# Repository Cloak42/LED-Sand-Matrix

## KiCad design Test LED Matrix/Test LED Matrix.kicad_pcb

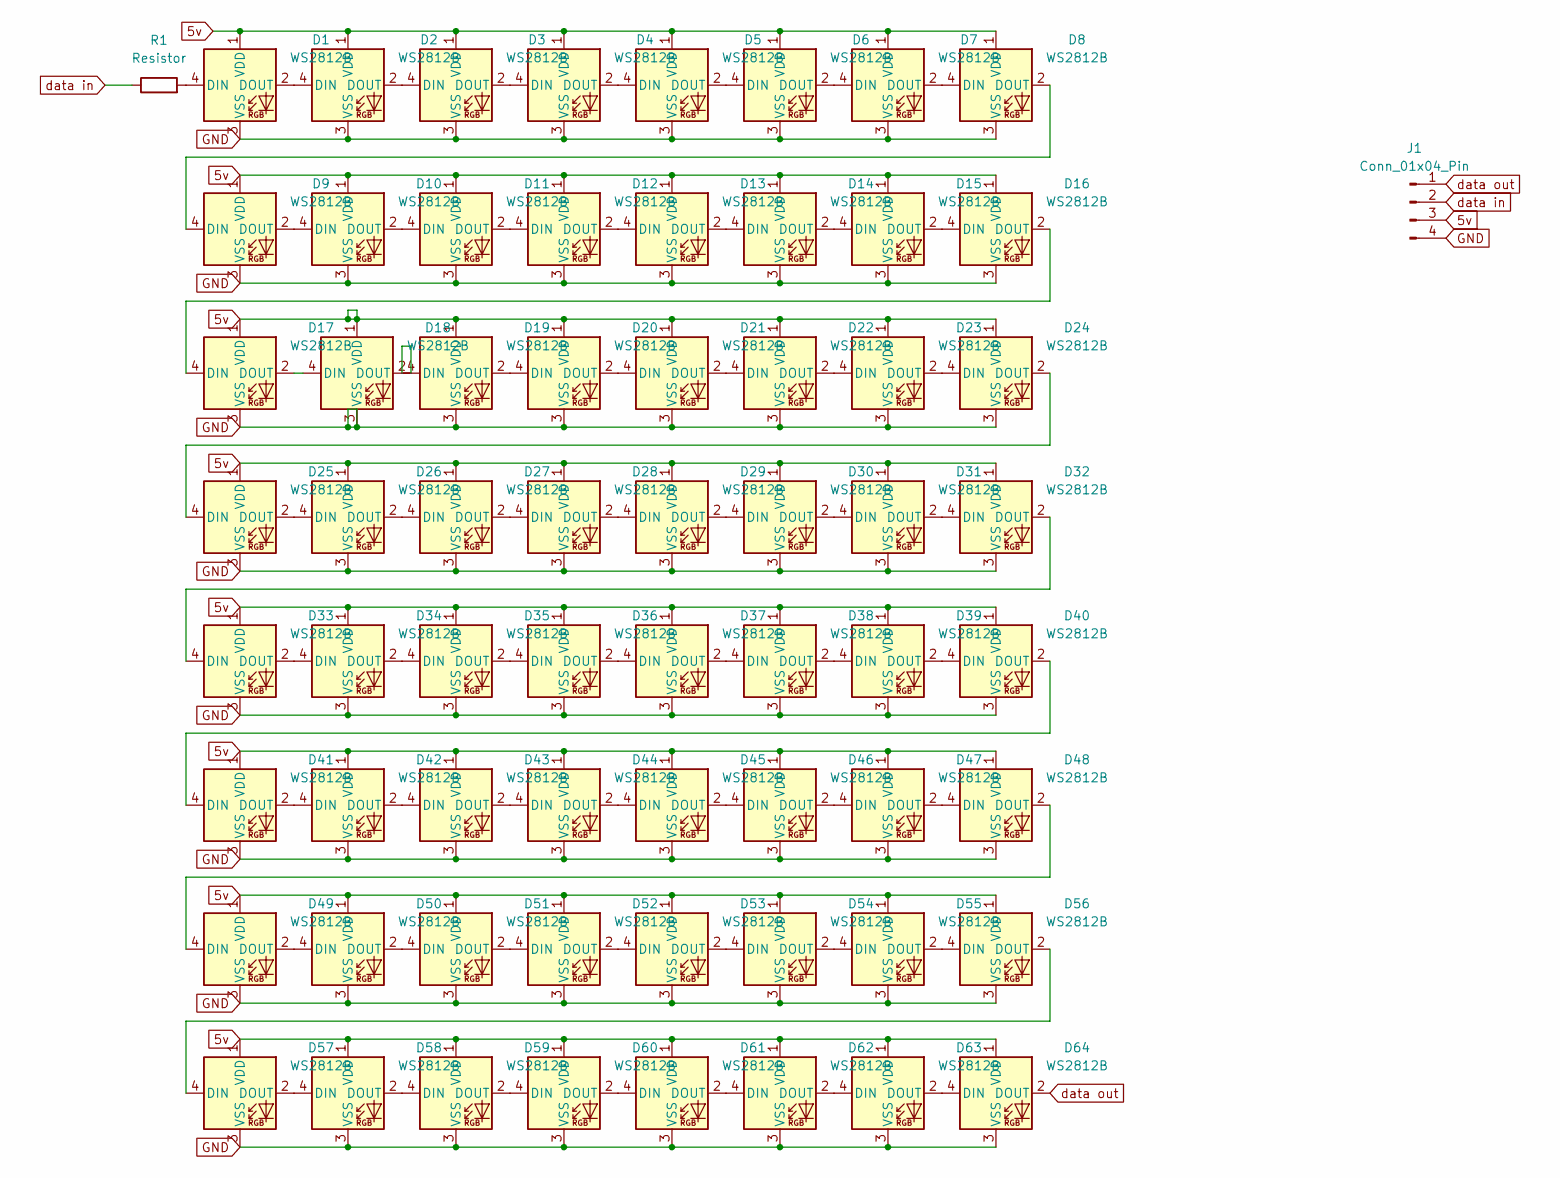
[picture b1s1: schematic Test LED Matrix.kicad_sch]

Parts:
D1, D2, D3, D4, D5, D6, D7, D8, D9, D10, D11, D12, D13, D14, D15, D16, D17, D18, D19, D20, D21, D22, D23, D24, D25, D26, D27, D28, D29, D30, D31, D32, D33, D34, D35, D36, D37, D38, D39, D40, D41, D42, D43, D44, D45, D46, D47, D48, D49, D50, D51, D52, D53, D54, D55, D56, D57, D58, D59, D60, D61, D62, D63, D64: WS2812B; LED_WS2812B_PLCC4_5.0x5.0mm_P3.2mm
J1: Conn_01x04_Pin; PinSocket_1x04_P2.54mm_Vertical
R1: Resistor; R_Axial_DIN0204_L3.6mm_D1.6mm_P5.08mm_Horizontal

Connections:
5v: D1.1 (VDD), D2.1 (VDD), D3.1 (VDD), D4.1 (VDD), D5.1 (VDD), D6.1 (VDD), D7.1 (VDD), D8.1 (VDD), D9.1 (VDD), D10.1 (VDD), D11.1 (VDD), D12.1 (VDD), D13.1 (VDD), D14.1 (VDD), D15.1 (VDD), D16.1 (VDD), D17.1 (VDD), D18.1 (VDD), D19.1 (VDD), D20.1 (VDD), D21.1 (VDD), D22.1 (VDD), D23.1 (VDD), D24.1 (VDD), D25.1 (VDD), D26.1 (VDD), D27.1 (VDD), D28.1 (VDD), D29.1 (VDD), D30.1 (VDD), D31.1 (VDD), D32.1 (VDD), D33.1 (VDD), D34.1 (VDD), D35.1 (VDD), D36.1 (VDD), D37.1 (VDD), D38.1 (VDD), D39.1 (VDD), D40.1 (VDD), D41.1 (VDD), D42.1 (VDD), D43.1 (VDD), D44.1 (VDD), D45.1 (VDD), D46.1 (VDD), D47.1 (VDD), D48.1 (VDD), D49.1 (VDD), D50.1 (VDD), D51.1 (VDD), D52.1 (VDD), D53.1 (VDD), D54.1 (VDD), D55.1 (VDD), D56.1 (VDD), D57.1 (VDD), D58.1 (VDD), D59.1 (VDD), D60.1 (VDD), D61.1 (VDD), D62.1 (VDD), D63.1 (VDD), D64.1 (VDD), J1.3
GND: D1.3 (VSS), D2.3 (VSS), D3.3 (VSS), D4.3 (VSS), D5.3 (VSS), D6.3 (VSS), D7.3 (VSS), D8.3 (VSS), D9.3 (VSS), D10.3 (VSS), D11.3 (VSS), D12.3 (VSS), D13.3 (VSS), D14.3 (VSS), D15.3 (VSS), D16.3 (VSS), D17.3 (VSS), D18.3 (VSS), D19.3 (VSS), D20.3 (VSS), D21.3 (VSS), D22.3 (VSS), D23.3 (VSS), D24.3 (VSS), D25.3 (VSS), D26.3 (VSS), D27.3 (VSS), D28.3 (VSS), D29.3 (VSS), D30.3 (VSS), D31.3 (VSS), D32.3 (VSS), D33.3 (VSS), D34.3 (VSS), D35.3 (VSS), D36.3 (VSS), D37.3 (VSS), D38.3 (VSS), D39.3 (VSS), D40.3 (VSS), D41.3 (VSS), D42.3 (VSS), D43.3 (VSS), D44.3 (VSS), D45.3 (VSS), D46.3 (VSS), D47.3 (VSS), D48.3 (VSS), D49.3 (VSS), D50.3 (VSS), D51.3 (VSS), D52.3 (VSS), D53.3 (VSS), D54.3 (VSS), D55.3 (VSS), D56.3 (VSS), D57.3 (VSS), D58.3 (VSS), D59.3 (VSS), D60.3 (VSS), D61.3 (VSS), D62.3 (VSS), D63.3 (VSS), D64.3 (VSS), J1.4
unnamed: D1.4 (DIN), R1.2
unnamed: D1.2 (DOUT), D2.4 (DIN)
unnamed: D2.2 (DOUT), D3.4 (DIN)
unnamed: D3.2 (DOUT), D4.4 (DIN)
unnamed: D4.2 (DOUT), D5.4 (DIN)
unnamed: D5.2 (DOUT), D6.4 (DIN)
unnamed: D6.2 (DOUT), D7.4 (DIN)
unnamed: D7.2 (DOUT), D8.4 (DIN)
unnamed: D8.2 (DOUT), D9.4 (DIN)
unnamed: D9.2 (DOUT), D10.4 (DIN)
unnamed: D10.2 (DOUT), D11.4 (DIN)
unnamed: D11.2 (DOUT), D12.4 (DIN)
unnamed: D12.2 (DOUT), D13.4 (DIN)
unnamed: D13.2 (DOUT), D14.4 (DIN)
unnamed: D14.2 (DOUT), D15.4 (DIN)
unnamed: D15.2 (DOUT), D16.4 (DIN)
unnamed: D16.2 (DOUT), D17.4 (DIN)
unnamed: D17.2 (DOUT), D18.4 (DIN)
unnamed: D18.2 (DOUT), D19.4 (DIN)
unnamed: D19.2 (DOUT), D20.4 (DIN)
unnamed: D20.2 (DOUT), D21.4 (DIN)
unnamed: D21.2 (DOUT), D22.4 (DIN)
unnamed: D22.2 (DOUT), D23.4 (DIN)
unnamed: D23.2 (DOUT), D24.4 (DIN)
unnamed: D24.2 (DOUT), D25.4 (DIN)
unnamed: D25.2 (DOUT), D26.4 (DIN)
unnamed: D26.2 (DOUT), D27.4 (DIN)
unnamed: D27.2 (DOUT), D28.4 (DIN)
unnamed: D28.2 (DOUT), D29.4 (DIN)
unnamed: D29.2 (DOUT), D30.4 (DIN)
unnamed: D30.2 (DOUT), D31.4 (DIN)
unnamed: D31.2 (DOUT), D32.4 (DIN)
unnamed: D32.2 (DOUT), D33.4 (DIN)
unnamed: D33.2 (DOUT), D34.4 (DIN)
unnamed: D34.2 (DOUT), D35.4 (DIN)
unnamed: D35.2 (DOUT), D36.4 (DIN)
unnamed: D36.2 (DOUT), D37.4 (DIN)
unnamed: D37.2 (DOUT), D38.4 (DIN)
unnamed: D38.2 (DOUT), D39.4 (DIN)
unnamed: D39.2 (DOUT), D40.4 (DIN)
unnamed: D40.2 (DOUT), D41.4 (DIN)
unnamed: D41.2 (DOUT), D42.4 (DIN)
unnamed: D42.2 (DOUT), D43.4 (DIN)
unnamed: D43.2 (DOUT), D44.4 (DIN)
unnamed: D44.2 (DOUT), D45.4 (DIN)
unnamed: D45.2 (DOUT), D46.4 (DIN)
unnamed: D46.2 (DOUT), D47.4 (DIN)
unnamed: D47.2 (DOUT), D48.4 (DIN)
unnamed: D48.2 (DOUT), D49.4 (DIN)
unnamed: D49.2 (DOUT), D50.4 (DIN)
unnamed: D50.2 (DOUT), D51.4 (DIN)
unnamed: D51.2 (DOUT), D52.4 (DIN)
unnamed: D52.2 (DOUT), D53.4 (DIN)
unnamed: D53.2 (DOUT), D54.4 (DIN)
unnamed: D54.2 (DOUT), D55.4 (DIN)
unnamed: D55.2 (DOUT), D56.4 (DIN)
unnamed: D56.2 (DOUT), D57.4 (DIN)
unnamed: D57.2 (DOUT), D58.4 (DIN)
unnamed: D58.2 (DOUT), D59.4 (DIN)
unnamed: D59.2 (DOUT), D60.4 (DIN)
unnamed: D60.2 (DOUT), D61.4 (DIN)
unnamed: D61.2 (DOUT), D62.4 (DIN)
unnamed: D62.2 (DOUT), D63.4 (DIN)
unnamed: D63.2 (DOUT), D64.4 (DIN)
data in: J1.2, R1.1
data out: D64.2 (DOUT), J1.1

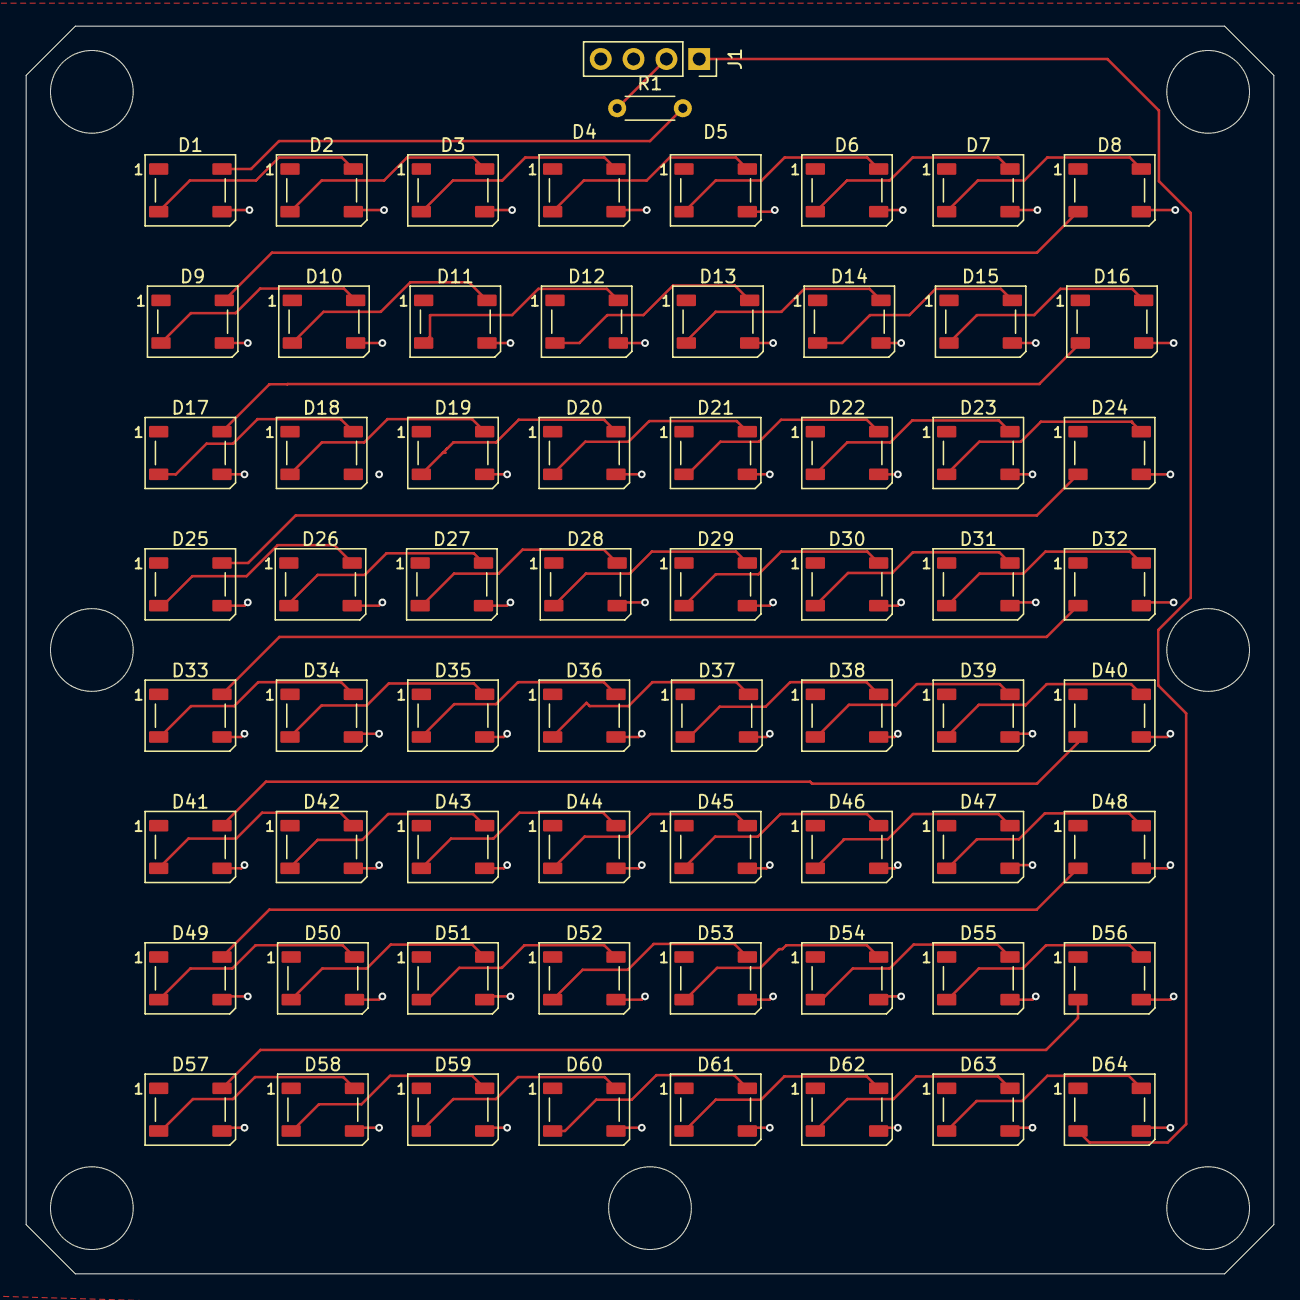
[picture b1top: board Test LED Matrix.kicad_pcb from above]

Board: 2 copper layers, 96.5 x 96.5 mm, 66 parts (0 on the bottom side), 68 nets.
